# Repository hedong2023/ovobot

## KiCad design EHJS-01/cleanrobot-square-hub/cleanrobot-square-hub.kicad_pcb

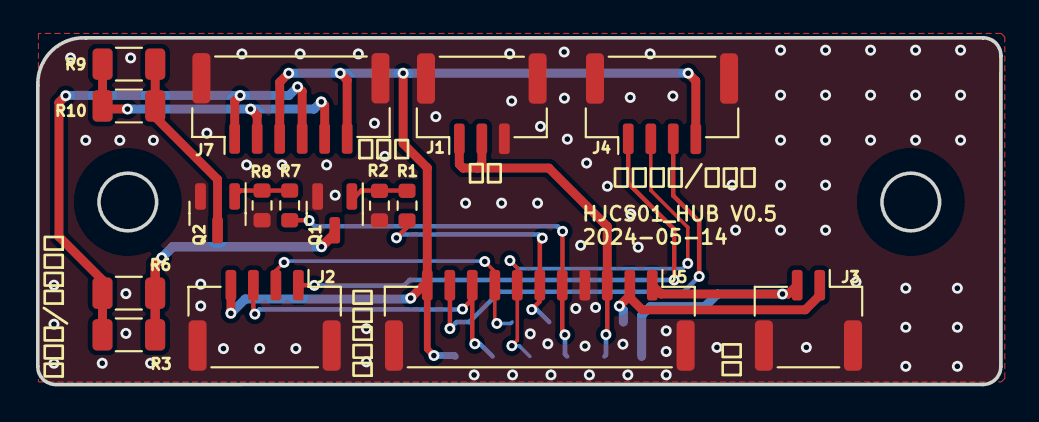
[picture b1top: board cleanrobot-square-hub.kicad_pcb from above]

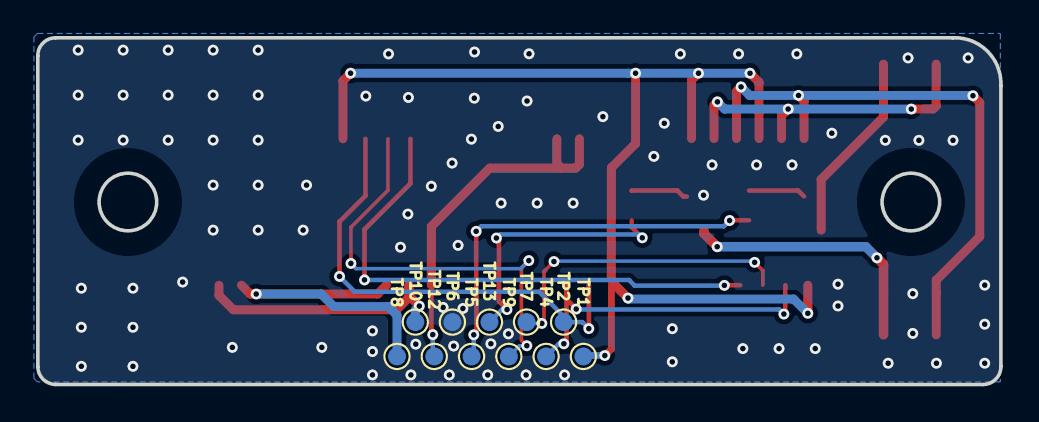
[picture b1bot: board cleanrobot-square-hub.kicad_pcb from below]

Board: 2 copper layers, 53.5 x 19.3 mm, 27 parts (11 on the bottom side), 18 nets.

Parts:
J1: GH1.25MM/3ASMT; JST_GH_BM03B-GHS-TBT_1x03-1MP_P1.25mm_Vertical
J2, J4: GH1.25MM/4ASMT; JST_GH_BM04B-GHS-TBT_1x04-1MP_P1.25mm_Vertical
J3: GH1.25MM/2ASMT; JST_GH_BM02B-GHS-TBT_1x02-1MP_P1.25mm_Vertical
J5: GH1.25MM/11ASMT; JST_GH_BM11B-GHS-TBT_1x11-1MP_P1.25mm_Vertical
J7: GH1.25MM/6ASMT; JST_GH_BM06B-GHS-TBT_1x06-1MP_P1.25mm_Vertical
Q1, Q2: SS8050; SOT-23
R1, R7: 1K; R_0603_1608Metric
R2, R8: 10K/1%; R_0603_1608Metric
R3, R6, R9, R10: 120R/250mW; R_1206_3216Metric
TP1: 5V; TestPoint_Pad_D1.0mm
TP2: SPRAY_FRONT; TestPoint_Pad_D1.0mm
TP4: SPRAY_BACK; TestPoint_Pad_D1.0mm
TP5: RED; TestPoint_Pad_D1.0mm
TP6: GND; TestPoint_Pad_D1.0mm
TP7: WATER1_DET_P; TestPoint_Pad_D1.0mm
TP8: SPEAKER_P; TestPoint_Pad_D1.0mm
TP9: WATER1_DET_N; TestPoint_Pad_D1.0mm
TP10: SPEAKER_N; TestPoint_Pad_D1.0mm
TP12: START; TestPoint_Pad_D1.0mm
TP13: GREEN; TestPoint_Pad_D1.0mm

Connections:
+5V: J2.4, J4.4, J5.11, J7.3, J7.6, TP1.1
/BLUE: J7.1, J7.4, R3.1, R6.1
/LED_BLUE: J5.6, R1.1, TP13.1
/LED_RED: J5.5, R7.1, TP5.1
/RED: J7.2, J7.5, R9.1, R10.1
/SPEAKER_N: J3.1, J5.2, TP10.1
/SPEAKER_P: J3.2, J5.1, TP8.1
/SPRAY_BACK: J2.3, J5.9, TP4.1
/SPRAY_FRONT: J4.3, J5.10, TP2.1
/START: J1.1, J1.2, J5.3, TP12.1
/WATER_COM: J2.1, J4.1
/WATER_DET_N: J4.2, J5.7, TP9.1
/WATER_DET_P: J2.2, J5.8, TP7.1
GND: J1.3, J1.MP (MountPin), J2.MP (MountPin), J3.MP (MountPin), J4.MP (MountPin), J5.4, J5.MP (MountPin), J7.MP (MountPin), Q1.2 (E), Q2.2 (E), R2.2, R8.2, TP6.1
unnamed: Q1.1 (B), R1.2, R2.1
unnamed: Q1.3 (C), R3.2, R6.2
unnamed: Q2.1 (B), R7.2, R8.1
unnamed: Q2.3 (C), R9.2, R10.2

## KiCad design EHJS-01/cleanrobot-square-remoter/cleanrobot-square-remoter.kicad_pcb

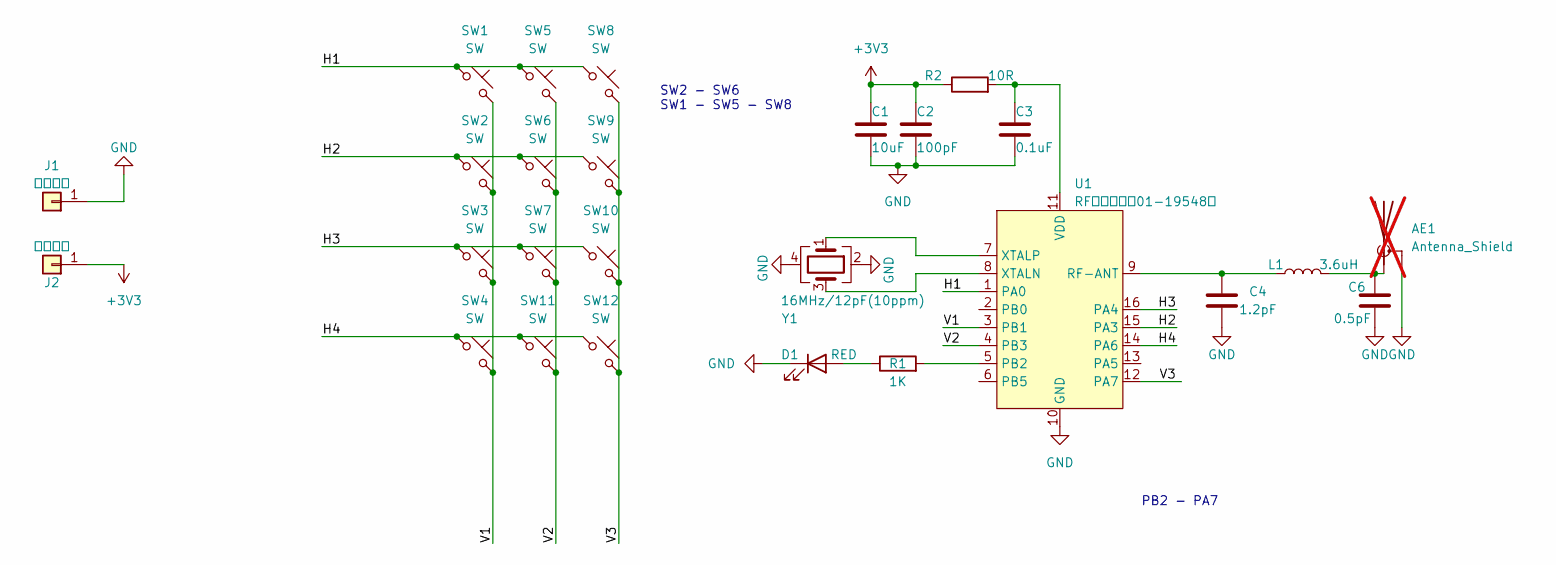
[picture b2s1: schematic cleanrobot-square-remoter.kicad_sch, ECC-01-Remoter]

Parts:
AE1: Antenna_Shield; Texas_SWRA117D_2.4GHz_Right; not fitted
C1: 10uF; C_0603_1608Metric
C2: 100pF; C_0603_1608Metric
C3: 0.1uF; C_0603_1608Metric
C4: 1.2pF; C_0603_1608Metric
C6: 0.5pF; C_0603_1608Metric
D1: RED; LED_1206_3216Metric
J1: 负极弹簧; Pad_THTPad_4.3x2.1mm_Drill3.1x0.9mm
J2: 正极弹簧; Pad_THTPad_4.3x2.1mm_Drill3.1x0.9mm
L1: 3.6uH; L_0603_1608Metric
R1: 1K; R_0603_1608Metric
R2: 10R; R_0603_1608Metric
SW1, SW2, SW3, SW4, SW5, SW6, SW7, SW8, SW9, SW10, SW11, SW12: SW; Dome_SLICE_ARC_6x6mm
U1: RF射频芯片（01-19548）; SOP-16_3.9x9.9mm_P1.27mm
Y1: 16MHz/12pF(10ppm); Oscillator_SMD_Abracon_ASE-4Pin_3.2x2.5mm

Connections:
+3V3: C1.1, C2.1, J2.1, R2.1
/H1: SW1.1, SW5.1, SW8.1, U1.1 (PA0)
/H2: SW2.1, SW6.1, SW9.1, U1.15 (PA3)
/H3: SW3.1, SW7.1, SW10.1, U1.16 (PA4)
/H4: SW4.1, SW11.1, SW12.1, U1.14 (PA6)
/V1: SW1.2, SW2.2, SW3.2, SW4.2, U1.3 (PB1)
/V2: SW5.2, SW6.2, SW7.2, SW11.2, U1.4 (PB3)
/V3: SW8.2, SW9.2, SW10.2, SW12.2, U1.12 (PA7)
GND: AE1.2 (Shield), C1.2, C2.2, C3.2, C4.1, C6.1, D1.1 (K), J1.1, U1.10 (GND), Y1.2, Y1.4
unnamed: AE1.1 (A), C6.2, L1.1
unnamed: D1.2 (A), R1.1
unnamed: R1.2, U1.5 (PB2)
unnamed: C4.2, L1.2, U1.9 (RF-ANT)
unnamed: C3.1, R2.2, U1.11 (VDD)
unnamed: U1.8 (XTALN), Y1.3
unnamed: U1.7 (XTALP), Y1.1

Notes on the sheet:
SW2 - SW6 SW1 - SW5 - SW8
PB2 - PA7

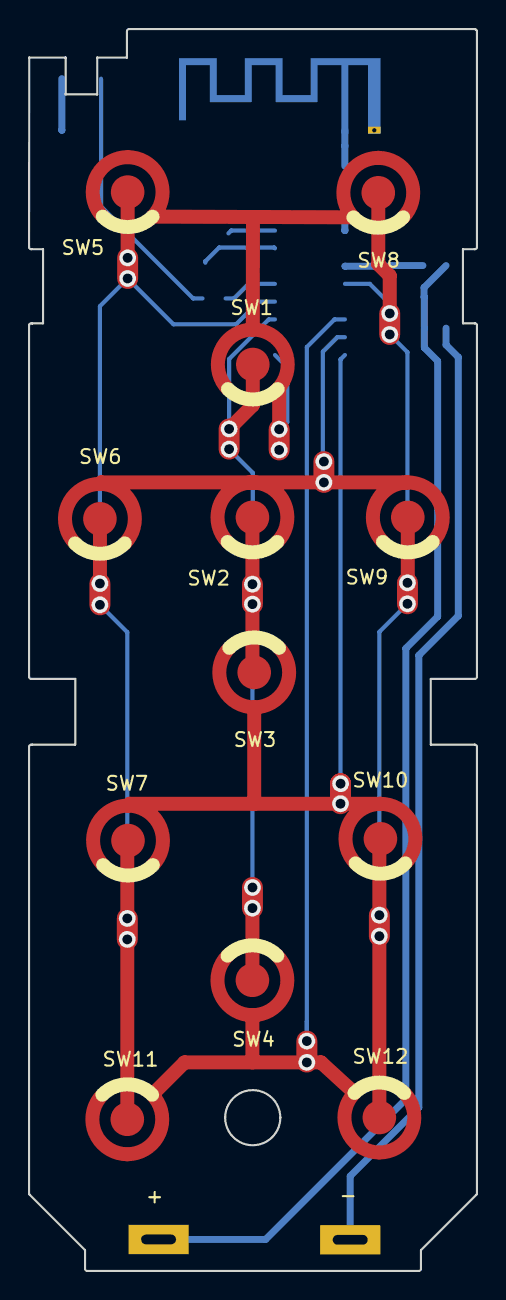
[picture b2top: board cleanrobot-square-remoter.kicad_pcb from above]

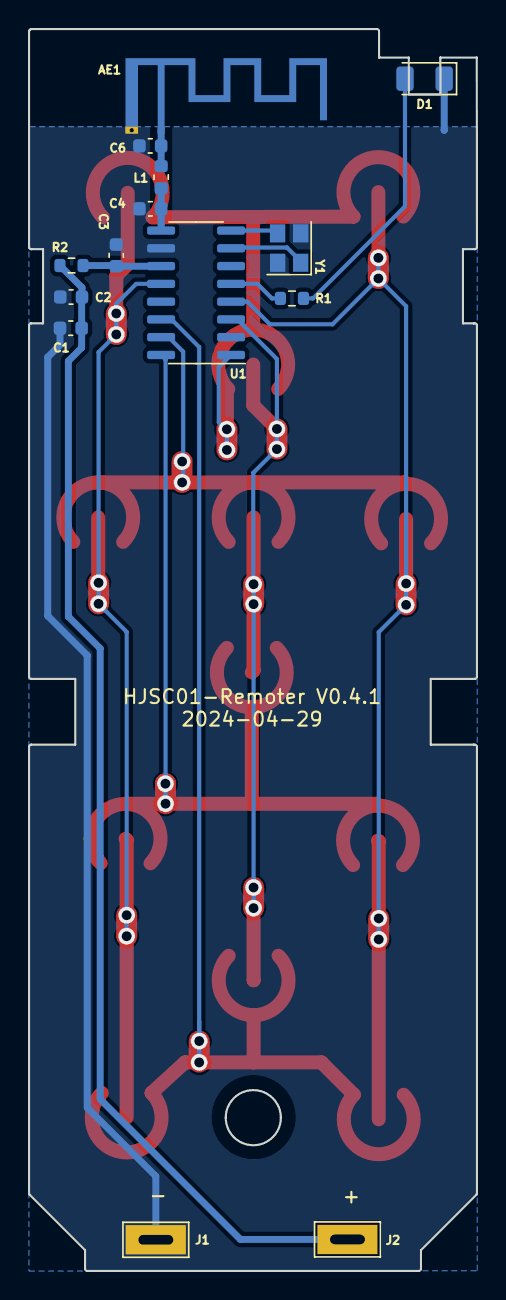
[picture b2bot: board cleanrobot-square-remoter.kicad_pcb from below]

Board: 2 copper layers, 32.0 x 88.7 mm, 26 parts (14 on the bottom side), 16 nets.

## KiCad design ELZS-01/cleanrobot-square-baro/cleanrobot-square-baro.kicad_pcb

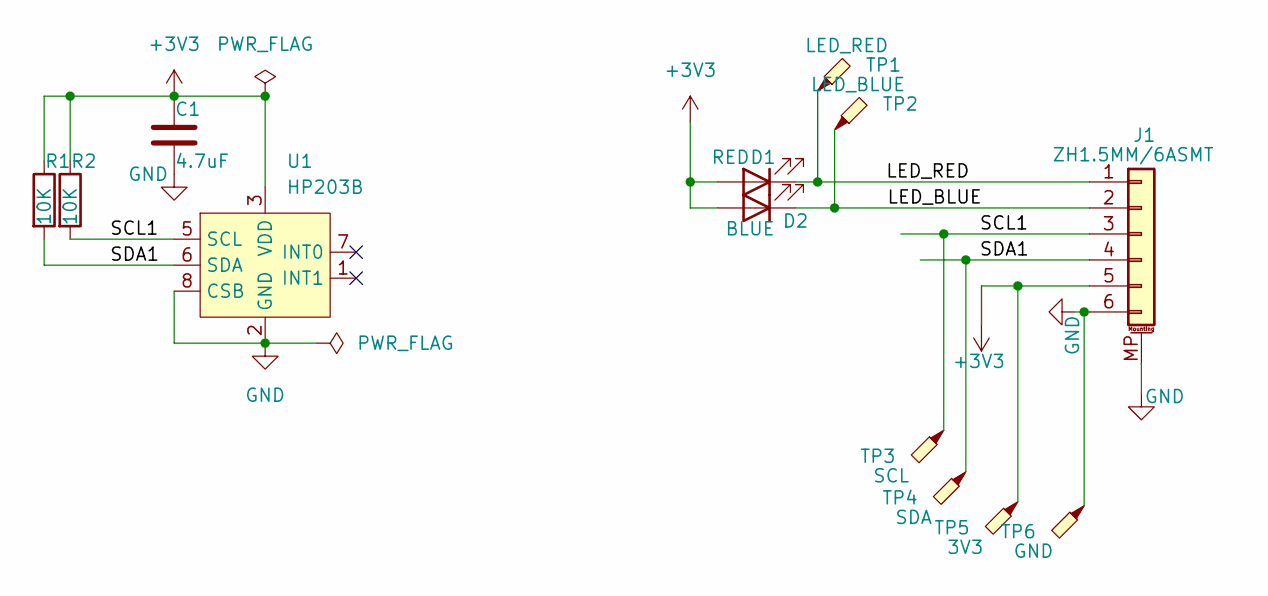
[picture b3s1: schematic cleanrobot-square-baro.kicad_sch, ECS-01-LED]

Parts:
C1: 4.7uF; C_0603_1608Metric
D1: RED; D_0603_1608Metric
D2: BLUE; D_0603_1608Metric
J1: ZH1.5MM/6ASMT; JST_ZH_B6B-ZR-SM4-TF_1x06-1MP_P1.50mm_Vertical
R1, R2: 10K; R_0603_1608Metric
TP1: LED_RED; TestPoint_Pad_D1.5mm
TP2: LED_BLUE; TestPoint_Pad_D1.5mm
TP3: SCL; TestPoint_Pad_D1.5mm
TP4: SDA; TestPoint_Pad_D1.5mm
TP5: 3V3; TestPoint_Pad_D1.5mm
TP6: GND; TestPoint_Pad_D1.5mm
U1: HP203B; HOPERF_LGA-8_3.8x3.6mm_P0.9mm

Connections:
+3V3: C1.1, D1.2 (A), D2.2 (A), J1.5, R1.1, R2.1, TP5.1, U1.3 (VDD)
/LED_BLUE: D2.1 (K), J1.2, TP2.1
/LED_RED: D1.1 (K), J1.1, TP1.1
/SCL1: J1.3, R2.2, TP3.1, U1.5 (SCL)
/SDA1: J1.4, R1.2, TP4.1, U1.6 (SDA)
GND: C1.2, J1.6, J1.MP (MountPin), TP6.1, U1.2 (GND), U1.8 (CSB)

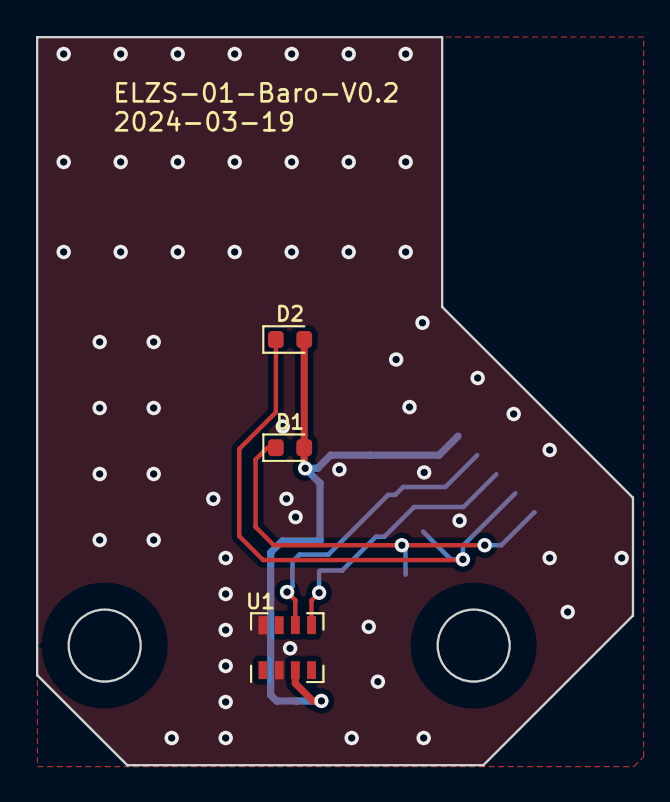
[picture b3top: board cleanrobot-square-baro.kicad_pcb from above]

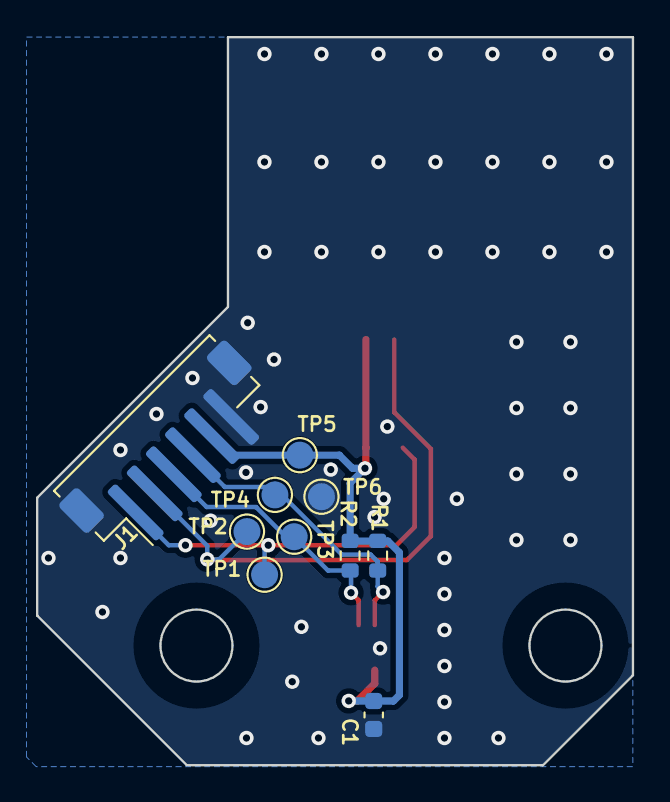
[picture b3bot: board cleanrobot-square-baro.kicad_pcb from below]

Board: 2 copper layers, 33.1 x 40.4 mm, 13 parts (10 on the bottom side), 6 nets.

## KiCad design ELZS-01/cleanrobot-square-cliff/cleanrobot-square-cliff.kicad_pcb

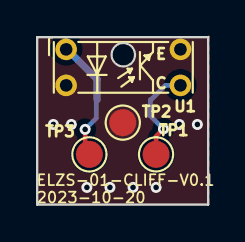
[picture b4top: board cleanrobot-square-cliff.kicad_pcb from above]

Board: 2 copper layers, 9.5 x 9.3 mm, 5 parts (1 on the bottom side), 3 nets.

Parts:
J1: SH1.25MM/3AWSMT; Molex_PicoBlade_53261-0371_1x03-1MP_P1.25mm_Horizontal
TP1: EDGE_DET_LT; TestPoint_Pad_D1.5mm
TP2: GND; TestPoint_Pad_D1.5mm
TP3: 3V3; TestPoint_Pad_D1.5mm
U1: ITR1203DT50A/TB; EverLight_ITR1203_7.5x2.6mm_P2.0mm

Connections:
/EDGE_DET_LT: J1.1, TP1.1, U1.3 (C)
GND: J1.2, J1.MP (MountPin), TP2.1, U1.2 (K), U1.4 (E)
unnamed: J1.3, TP3.1, U1.1 (A)

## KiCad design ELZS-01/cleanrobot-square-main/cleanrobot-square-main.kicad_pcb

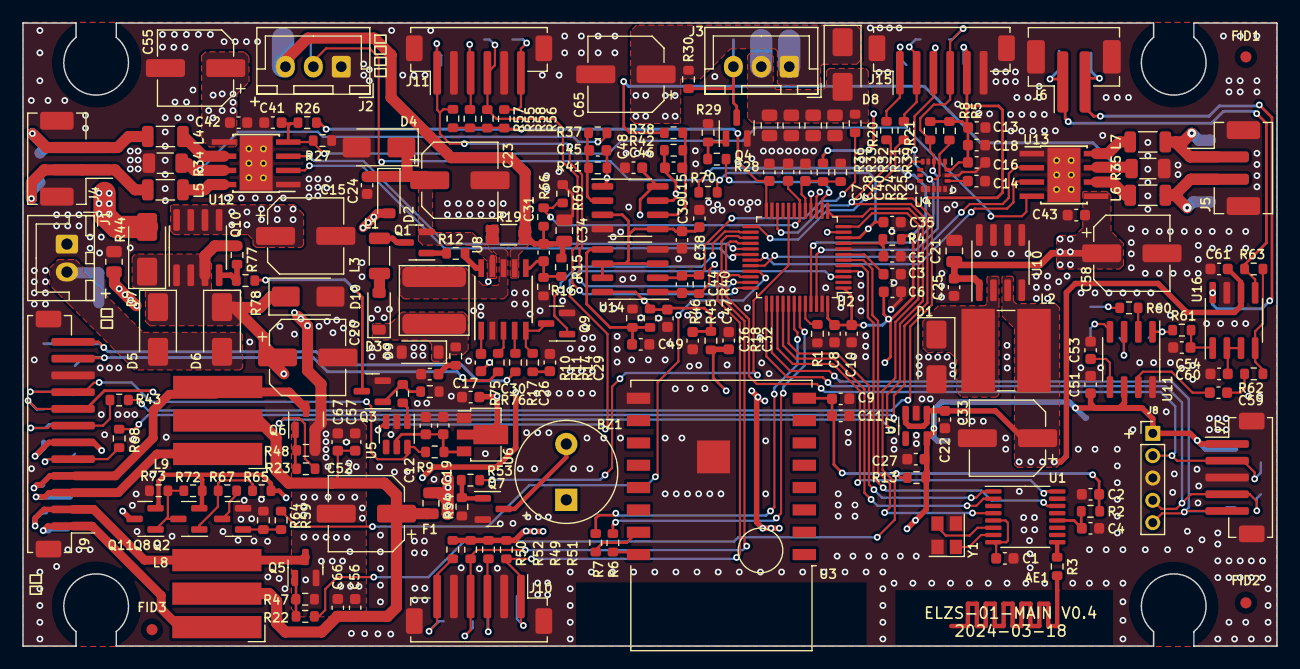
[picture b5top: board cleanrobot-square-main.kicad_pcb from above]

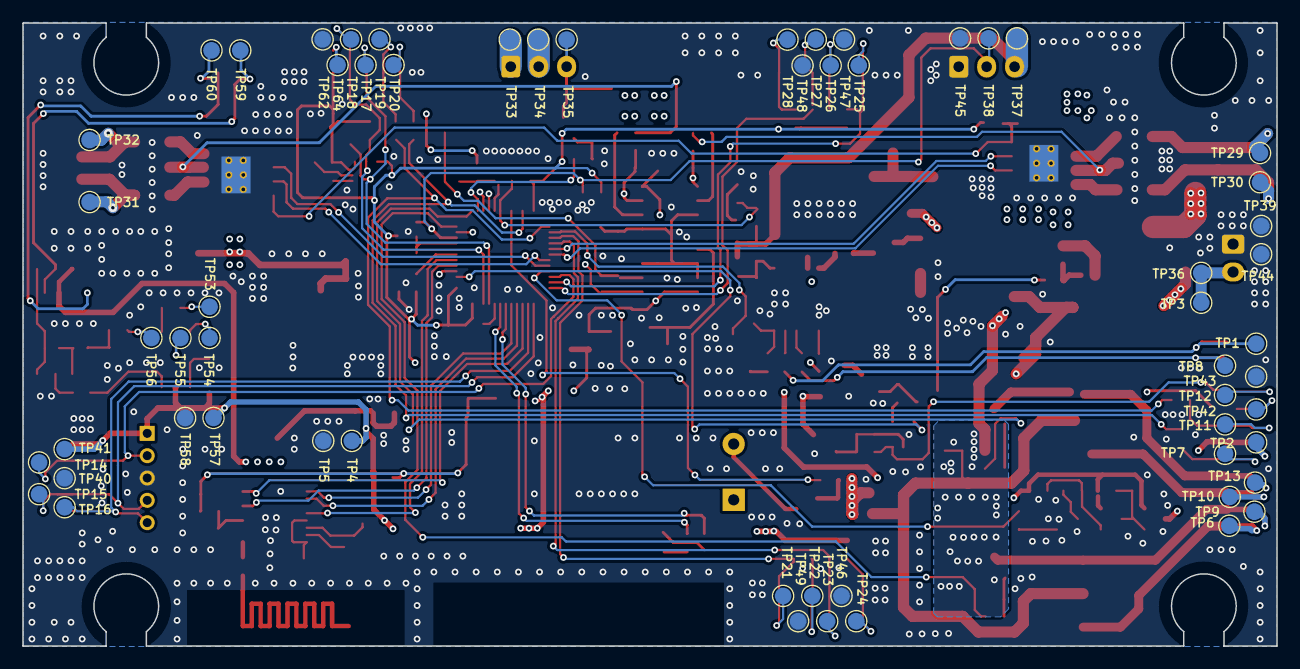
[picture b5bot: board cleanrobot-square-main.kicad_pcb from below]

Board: 4 copper layers, 112.3 x 55.8 mm, 261 parts (59 on the bottom side), 134 nets.

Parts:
AE1: NC/Antenna; Ovo_PA2401_2.4GHz_Right
BZ1: 85dB/5V; Buzzer_9x5.5RM5
C1, C2, C9, C22, C25, C27, C32, C36, C54, C56, C57, C60, C61: 1uF; C_0603_1608Metric
C3, C4, C5, C6, C7, C8, C11, C12, C16, C17, C24, C26, C28, C35, C38, C40, C41, C42, C43, C44, C45, C46, C47, C48, C49, C66, C67: 0.1uF; C_0603_1608Metric
C10: 4.7uF; C_0603_1608Metric
C13, C39: 10nF; C_0603_1608Metric
C14, C59: 0.47uF; C_0603_1608Metric
C15, C20, C55, C58, C65: 100uF/35V; CP_Elec_6.3x7.7
C18: 2.2uF; C_0603_1608Metric
C19, C51: 10uF; C_0603_1608Metric
C21, C34: 10uF/35V; C_0805_2012Metric
C23: 100uF/50V; CP_Elec_6.3x7.7
C29: 220nF; C_0603_1608Metric
C30, C53: 1nF; C_0603_1608Metric
C31: 1.5pF; C_0603_1608Metric
C33, C52: 470uF/10V; CP_Elec_6.3x7.7
D1, D5, D6, D7: SS34; D_SMA
D2, D3, D9: SS14; D_SOD-123
D4, D10: SMAJ24CA; D_SMA
D8: 1N4004; D_SMA
F1: MF-PSMF050X; Fuse_0805_2012Metric
FID1, FID2, FID3: NC/Fiducial; Fiducial_1mm_Mask2mm
J1: XHB2.54MM/2A; JST_XH_B2B-XH-A_1x02_P2.50mm_Vertical
J2, J3: XH2.54MM/3A; JST_XH_B3B-XH-A_1x03_P2.50mm_Vertical
J4, J5, J6: PH2.0MM/2ASMT; JST_PH_B2B-PH-SM4-TB_1x02-1MP_P2.00mm_Vertical
J7: ZH1.5MM/5ASMT; JST_ZH_B5B-ZR-SM4-TF_1x05-1MP_P1.50mm_Vertical
J8: 2.0MM/5ASMT; PinHeader_1x05_P2.00mm_Vertical
J9: ZH1.5MM/12ASMT; JST_ZH_B12B-ZR-SM4-TF_1x12-1MP_P1.50mm_Vertical
J10, J11, J15: ZH1.5MM/6ASMT; JST_ZH_B6B-ZR-SM4-TF_1x06-1MP_P1.50mm_Vertical
L1, L4, L5, L6, L7: 120R@100MHz/3A; L_1206_3216Metric
L2: 68uH; L_GZJ_CD75
L3: 100uH; L_GZJ_WNR6045
L8, L9: 10/500uH; L_WLJ_CD0805
Q1: HSS6107; SOT-23
Q2, Q3, Q4, Q7: SS8050; SOT-23
Q5, Q6: CJ2310; SOT-23
Q8: SS8550; SOT-23
Q9: SI2302; SOT-23
Q10: NCE40P13S; SOIC-8_3.9x4.9mm_P1.27mm
Q11: SI2309; SOT-23
R1, R9, R10, R11, R29, R45, R47, R48, R51, R52, R54, R57, R58, R61, R62, R63, R64, R70, R76, R77, R78: 10K/1%; R_0603_1608Metric
R2, R3, R4, R6, R7, R13, R18, R60: 0R; R_0603_1608Metric
R5, R8: 4.7K/1%; R_0603_1608Metric
R12: 51R; R_0603_1608Metric
R14, R49, R50, R55, R56: 120R; R_0603_1608Metric
R15: 1.5M/1%; R_0603_1608Metric
R16: 120K/1%; R_0603_1608Metric
R17: 100R; R_0603_1608Metric
R19: 0.5R/1%; R_1206_3216Metric
R20, R21, R43, R68: 330R; R_0603_1608Metric
R22, R23, R28, R53, R59, R75: 1K; R_0603_1608Metric
R24, R66: 1M/1%; R_0603_1608Metric
R25, R69: 100K/1%; R_0603_1608Metric
R26: 6.8K/1%; R_0603_1608Metric
R27: 3.3K/1%; R_0603_1608Metric
R30: NC/10K/1%; R_0603_1608Metric
R31, R32, R33, R36: 0.1R; R_0805_2012Metric
R34, R35: 0.033R/1%(1W); R_1206_3216Metric
R37, R38, R39: 15K/1%; R_0603_1608Metric
R40, R41, R42: 51K/1%; R_0603_1608Metric
R44: 0R; R_0805_2012Metric
R46: 2K/1%; R_0603_1608Metric
R65, R73: 10K; R_0603_1608Metric
R67: 100K; R_0603_1608Metric
R72: 2K; R_0603_1608Metric
TP1: CHG_DONE_LED; TestPoint_Pad_D1.5mm
TP2: V_CHRG_O; TestPoint_Pad_D1.5mm
TP3, TP36: 24V; TestPoint_Pad_D1.5mm
TP4, TP57: 3V3; TestPoint_Pad_D1.5mm
TP5, TP39, TP40, TP43, TP44, TP45, TP46, TP47, TP48, TP49, TP58, TP62: GND; TestPoint_Pad_D1.5mm
TP6: SPRAY_FRONT_P; TestPoint_Pad_D1.5mm
TP7: LED_RED; TestPoint_Pad_D1.5mm
TP8: CHG_ON_LED; TestPoint_Pad_D1.5mm
TP9: SPRAY_FRONT_N; TestPoint_Pad_D1.5mm
TP10: SPRAY_BACK_P; TestPoint_Pad_D1.5mm
TP11: LED_BLUE; TestPoint_Pad_D1.5mm
TP12: START; TestPoint_Pad_D1.5mm
TP13: SPRAY_BACK_N; TestPoint_Pad_D1.5mm
TP14: SWDIO; TestPoint_Pad_D1.5mm
TP15: SWCLK; TestPoint_Pad_D1.5mm
TP16: UART2_RX; TestPoint_Pad_D1.5mm
TP17: SCL1; TestPoint_Pad_D1.5mm
TP18: SDA1; TestPoint_Pad_D1.5mm
TP19: BLUE; TestPoint_Pad_D1.5mm
TP20: RED; TestPoint_Pad_D1.5mm
TP21: EDGE_DET_LT; TestPoint_Pad_D1.5mm
TP22: EDGE_DET_LT_LED; TestPoint_Pad_D1.5mm
TP23: EDGE_DET_RT; TestPoint_Pad_D1.5mm
TP24: EDGE_DET_RT_LED; TestPoint_Pad_D1.5mm
TP25: EDGE_DET_LB; TestPoint_Pad_D1.5mm
TP26: EDGE_DET_LB_LED; TestPoint_Pad_D1.5mm
TP27: EDGE_DET_RB; TestPoint_Pad_D1.5mm
TP28: EDGE_DET_RB_LED; TestPoint_Pad_D1.5mm
TP29: MOTOR_LF_OUT1; TestPoint_Pad_D1.5mm
TP30: MOTOR_LF_OUT2; TestPoint_Pad_D1.5mm
TP31: MOTOR_RT_OUT1; TestPoint_Pad_D1.5mm
TP32: MOTOR_RT_OUT2; TestPoint_Pad_D1.5mm
TP33: VDD; TestPoint_Pad_D1.5mm
TP34: FAN_OUT_N; TestPoint_Pad_D1.5mm
TP35: FAN_OUT_PWM; TestPoint_Pad_D1.5mm
TP37: BATT; TestPoint_Pad_D1.5mm
TP38: TEMP; TestPoint_Pad_D1.5mm
TP41, TP42, TP64: +3V3; TestPoint_Pad_D1.5mm
TP53: DO; TestPoint_Pad_D1.5mm
TP54: CLK; TestPoint_Pad_D1.5mm
TP55: DI; TestPoint_Pad_D1.5mm
TP56: CS; TestPoint_Pad_D1.5mm
TP59: SPEAKER_P; TestPoint_Pad_D1.5mm
TP60: SPEAKER_N; TestPoint_Pad_D1.5mm
U1: LT8920; TSSOP-16_4.4x5mm_P0.65mm
U2: MM32F0144C6P; LQFP-48_7x7mm_P0.5mm
U3: BT3L; Tuya_BT3L
U4: MPU-6887; LGA-16_3x3mm_P0.5mm_LayoutBorder3x5y
U5: PMS150C-U06(0x2B191B); SOT-23-6
U6: HT7533-1-SOT89; SOT-89-3
U7: RT9013-33; SOT-23-5
U8: CN3765; SSOP-10_3.9x4.9mm_P1.00mm
U10: XL1509-5.0E1; SOIC-8_3.9x4.9mm_P1.27mm
U11: WT588F02B-8S-B2(通用); SOIC-8_3.9x4.9mm_P1.27mm
U12, U13: DRV8870DDA; Texas_HTSOP-8-1EP_3.9x4.9mm_P1.27mm_EP2.95x4.9mm_Mask2.4x3.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
U14, U15: LMV358TP-SR; SOIC-8_3.9x4.9mm_P1.27mm
U16: 8002A; SOIC-8_3.9x4.9mm_P1.27mm
Y1: 12MHz/22pF(10ppm); Oscillator_SMD_Abracon_ASE-4Pin_3.2x2.5mm

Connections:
+3.3VA: C36.1, C47.1, C48.1, R18.2, R45.1, U14.8 (V+), U15.8 (V+)
+3.3VP: C2.1, C9.1, C11.1, R2.1, R13.2, U3.8 (VDD_BAT)
+3V3: C6.2, C7.2, C8.2, C10.2, C13.2, C16.2, C18.2, C27.1, C32.1, C51.1, J7.1, J8.1, J9.8, J15.5, R4.2, R5.2, R8.2, R13.1, R18.1, R26.1, R49.1, R50.1, R51.1, R52.1, R55.1, R56.1, R57.1, R58.1, R70.1, TP4.1, TP41.1, TP42.1, TP57.1, TP64.1, U2.1 (VDD), U2.24 (VDD), U2.48 (VDD), U4.1 (VDDIO), U4.5 (CS), U4.16 (VDD), U7.5 (VOUT), U11.6 (VDD)
+5V: BZ1.1 (-), C22.1, C33.1, C61.1, F1.1, L2.2, U7.1 (VIN), U7.3 (EN), U10.3 (FB), U16.6 (VDD)
+24V: D2.2 (A), D5.2 (A), D6.2 (A), J1.2, TP3.1, TP36.1
+BATT: C31.1, C34.1, D7.2 (A), J2.3, R15.1, R19.2, R66.1, TP37.1, U8.7 (BAT)
/driver/VREF55: C38.1, C39.1, U14.3 (+), U14.6 (-), U14.7, U15.3 (+), U15.5 (+)
/main/BLE_MCU_RXD: R6.2, U2.43 (PB7)
/main/BLE_MCU_TXD: R7.2, U2.42 (PB6)
/main/MISO: U1.2 (MISO), U2.40 (PB4)
/main/MOSI: U1.1 (MOSI), U2.41 (PB5)
/main/RF_REST: U1.4 (~RST), U2.6 (PF1)
/main/SCK: U1.16 (SCK), U2.39 (PB3)
/main/SCS: U1.14 (SS), U2.5 (PF0)
/peripheral/VOICE_BUSY: R61.1, TP56.1, U11.1 (PC2/CS)
/peripheral/V_CHRG_O: J9.6, Q11.3 (D), TP2.1
/power/3V3_OFF: C12.1, C19.1, R9.1, U5.5 (VDD), U6.3 (VOUT)
/power/VIN: C17.1, C20.1, D5.1 (K), D6.1 (K), D7.1 (K), D10.1 (K), Q10.1 (S), Q10.2 (S), Q10.3 (S), R77.2, U6.2 (VIN)
ADC_BATT: C28.1, R66.2, R69.1, U2.18 (PB0)
ADC_FAN_MOTOR: C44.2, R40.2, U2.11 (PA1), U14.1
ADC_LEFT_MOTOR: C45.2, R41.2, U2.15 (PA5), U15.1
ADC_RIGHT_MOTOR: C46.2, R42.2, U2.16 (PA6), U15.7
ADC_SYS: C40.1, R24.2, R25.1, U2.17 (PA7)
BELL: R53.1, U2.20 (PB2)
CHG_DONE_LED: J9.12, R11.1, TP1.1
CHG_LED_SW: R59.1, U2.33 (PA12)
CHG_ON_LED: J9.11, R10.1, TP8.1
EDGE_DET_LB: J11.1, R57.2, TP25.1, U2.35 (PF6)
EDGE_DET_LT: J10.1, R51.2, TP21.1, U2.27 (PB14)
EDGE_DET_RB: J11.4, R58.2, TP27.1, U2.36 (PF7)
EDGE_DET_RT: J10.4, R52.2, TP23.1, U2.28 (PB15)
EN_CHRG: Q9.1 (G), U2.26 (PB13)
GND: C1.2, C2.2, C3.1, C4.2, C5.1, C6.1, C7.1, C8.1, C9.2, C10.1, C11.2, C12.2, C13.1, C14.1, C15.2, C16.1, C17.2, C18.1, C19.2, C20.2, C21.2, C22.2, C23.2, C24.2, C25.2, C27.2, C28.2, C29.2, C30.2, C32.2, C33.2, C34.2, C35.2, C36.2, C38.2, C39.2, C40.2, C41.2, C42.2, C43.2, C47.2, C48.2, C49.2, C51.2, C53.2, C54.2, C55.2, C58.2, C60.1, C61.2, C65.2, D1.2 (A), D4.2 (A), D9.2 (A), D10.2 (A), J1.1, J2.1, J4.MP (MountPin), J5.MP (MountPin), J6.MP (MountPin), J7.3, J7.MP (MountPin), J8.3, J9.10, J9.MP (MountPin), J10.2, J10.5, J10.MP (MountPin), J11.2, J11.5, J11.MP (MountPin), J15.6, J15.MP (MountPin), Q2.2 (E), Q3.2 (E), Q4.2 (E), Q7.2 (E), Q9.2 (S), R1.1, R16.2, R25.2, R27.2, R29.1, R31.2, R32.2, R33.2, R34.2, R35.2, R36.2, R44.2, R46.2, R54.2, R64.2, R69.2, R73.1, R76.1, TP5.1, TP39.1, TP40.1, TP43.1, TP44.1, TP45.1, TP46.1, TP47.1, TP48.1, TP49.1, TP58.1, TP62.1, U1.15 (VSS), U2.8 (VSSA), U2.23 (VSS), U2.47 (VSS), U3.9 (GND), U3.17 (PAD), U4.4 (AD0/SDO), U4.9 (RESV), U4.10 (RESV), U4.11 (RESV), U4.12 (RESV), U4.13 (GND), U4.15 (RECV), U5.2 (GND), U6.1 (GND), U7.2 (GND), U8.2 (GND), U10.4 (EN), U10.5 (GND), U10.6 (GND), U10.7 (GND), U10.8 (GND), U11.8 (GND), U12.1 (GND), U12.9 (GND), U13.1 (GND), U13.9 (GND), U14.4 (V-), U15.4 (V-), U16.7 (GND), Y1.2, Y1.4
GNDA: C52.2, C56.2, C57.2, C66.2, C67.2, Q5.2 (S), Q6.2 (S), R44.1, R47.2, R48.2
LED_BLUE: R21.1, R43.1, U2.25 (PB12)
LED_RED: R20.1, R68.1, U2.22 (PB11)
unnamed: AE1.1 (A), R3.2
unnamed: BZ1.2 (+), Q7.3 (C)
unnamed: C29.1, R14.2
unnamed: C30.1, R17.2
unnamed: C52.1, C56.1, C57.1, C66.1, C67.1, F1.2, L8.1, L9.1
unnamed: C59.2, R62.1
unnamed: D1.1 (K), L2.1, U10.2 (OUT)
unnamed: D3.2 (A), L1.2
unnamed: D3.1 (K), D9.1 (K), L3.1, R17.1
unnamed: D8.2 (A), J3.2, R31.1, R32.1, R33.1, R36.1, R39.1, TP34.1
unnamed: J3.3, Q4.3 (C), R30.2, TP35.1
unnamed: J4.1, L5.2, TP30.1
unnamed: J4.2, L4.2, TP29.1
unnamed: J5.1, L7.2, TP32.1
unnamed: J5.2, L6.2, TP31.1
unnamed: J6.1, R63.2, TP59.1, U16.5 (VO1)
unnamed: J6.2, TP60.1, U16.8 (VO2)
unnamed: J9.5, R68.2, TP7.1
unnamed: J9.7, R43.2, TP11.1
unnamed: J10.3, R49.2, TP22.1
unnamed: J10.6, R50.2, TP24.1
unnamed: J11.3, R55.2, TP26.1
unnamed: J11.6, R56.2, TP28.1
unnamed: J15.1, R20.2, TP20.1
unnamed: J15.2, R21.2, TP19.1
unnamed: L1.1, Q1.3 (D)
unnamed: Q1.1 (G), R12.1
unnamed: Q2.1 (B), R59.2, R64.1
unnamed: Q2.3 (C), R67.1
unnamed: Q3.1 (B), R75.1, R76.2
unnamed: Q3.3 (C), R78.1
unnamed: Q4.1 (B), R28.2, R29.2
unnamed: Q5.1 (G), R22.2, R47.1
unnamed: Q6.1 (G), R23.2, R48.1
unnamed: Q7.1 (B), R53.2, R54.1
unnamed: Q8.1 (B), R65.1, R67.2
unnamed: Q9.3 (D), R14.1, U8.5 (COM)
unnamed: Q10.4 (G), R77.1, R78.2
unnamed: Q8.3 (C), Q11.1 (G), R72.1, R73.2
unnamed: R3.1, U1.9 (ANTB)
unnamed: C4.1, R2.2, U1.12 (LDO_IN)
unnamed: C1.1, U1.5 (LDO_OUT), U1.8 (PLL_VDD)
unnamed: U1.7 (XTALI), Y1.1
unnamed: U1.6 (XTALO), Y1.3
unnamed: R1.2, U2.44 (BOOT0)
unnamed: C3.2, U2.7 (NRST)
unnamed: C5.2, R4.1, U2.9 (VDDA)
unnamed: R6.1, U3.16 (TL_B1)
unnamed: R7.1, U3.15 (TL_B7)
unnamed: C14.2, U4.14 (REGOUT)
unnamed: R75.2, U5.1 (PA4)
unnamed: L3.2, R19.1, U8.8 (CSP)
unnamed: R12.2, U8.10 (DRV)
unnamed: C31.2, R15.2, R16.1, U8.6 (FB)
unnamed: C26.2, U8.1 (VG)
unnamed: R10.2, U8.3 (~CHRG)
unnamed: R11.2, U8.4 (~DONE)
unnamed: R60.2, U11.2 (PC1/SO)
unnamed: TP55.1, U11.3 (PI0/SI)
unnamed: TP54.1, U11.4 (PI1/SCK)
unnamed: C53.1, U11.5 (PWMN)
unnamed: C59.1, U11.7 (PWMP/DAC)
unnamed: R34.1, R37.1, U12.7 (ISEN)
unnamed: L4.1, U12.6 (OUT1)
unnamed: L5.1, U12.8 (OUT2)
unnamed: C41.1, R26.2, R27.1, U12.4 (VREF), U13.4 (VREF)
unnamed: R35.1, R38.1, U13.7 (ISEN)
unnamed: L6.1, U13.6 (OUT1)
unnamed: L7.1, U13.8 (OUT2)
unnamed: C44.1, R39.2, R40.1, U14.2 (-)
unnamed: C49.1, R45.2, R46.1, U14.5 (+)
unnamed: C45.1, R37.2, R41.1, U15.2 (-)
unnamed: C46.1, R38.2, R42.1, U15.6 (-)
unnamed: C60.2, U16.2 (BYPASS), U16.3 (IN+)
unnamed: R62.2, R63.1, U16.4 (IN-)
unnamed: C54.1, R61.2, U16.1 (~SD)
PWM_FAN: R28.1, U2.14 (PA4)
PWM_LEFT1: U2.29 (PA8), U12.3 (IN1)
PWM_LEFT2: U2.30 (PA9), U12.2 (IN2)
PWM_RIGHT1: U2.31 (PA10), U13.3 (IN1)
PWM_RIGHT2: U2.32 (PA11), U13.2 (IN2)
SCL1: J15.3, R5.1, TP17.1, U2.45 (PB8), U4.2 (SCL/SCLK)
SDA1: J15.4, R8.1, TP18.1, U2.46 (PB9), U4.3 (SDA/SDI)
SPRAY_BACK: R23.1, U2.13 (PA3)
SPRAY_BACK_N: J9.4, L9.2, Q6.3 (D), TP13.1
SPRAY_BACK_P: J9.3, L9.3, TP10.1
SPRAY_FRONT: R22.1, U2.12 (PA2)
SPRAY_FRONT_N: J9.2, L8.2, Q5.3 (D), TP9.1
SPRAY_FRONT_P: J9.1, L8.3, TP6.1
START: J9.9, R9.2, TP12.1, U5.6 (PA3)
SWCLK: J7.4, J8.4, TP15.1, U2.37 (PA14)
SWDIO: J7.2, J8.2, TP14.1, U2.34 (PA13)
TEMP: C35.1, J2.2, R70.2, TP38.1, U2.10 (PA0)
TSD_DATA: U2.3 (PC14), U5.3 (PA6)
UART2_RX: J7.5, J8.5, TP16.1, U2.38 (PA15)
VDD: C15.1, C21.1, C25.1, C42.1, C43.1, C55.1, C58.1, C65.1, D8.1 (K), J3.1, Q10.5 (D), Q10.6 (D), Q10.7 (D), Q10.8 (D), R24.1, R30.1, TP33.1, U10.1 (VIN), U12.5 (VM), U13.5 (VM)
VOICE_DATA: R60.1, TP53.1, U2.4 (PC15)
V_CHRG_I: C23.1, C24.1, C26.1, D2.1 (K), D4.1 (K), Q1.2 (S), Q8.2 (E), Q11.2 (S), R65.2, R72.2, U8.9 (VCC)

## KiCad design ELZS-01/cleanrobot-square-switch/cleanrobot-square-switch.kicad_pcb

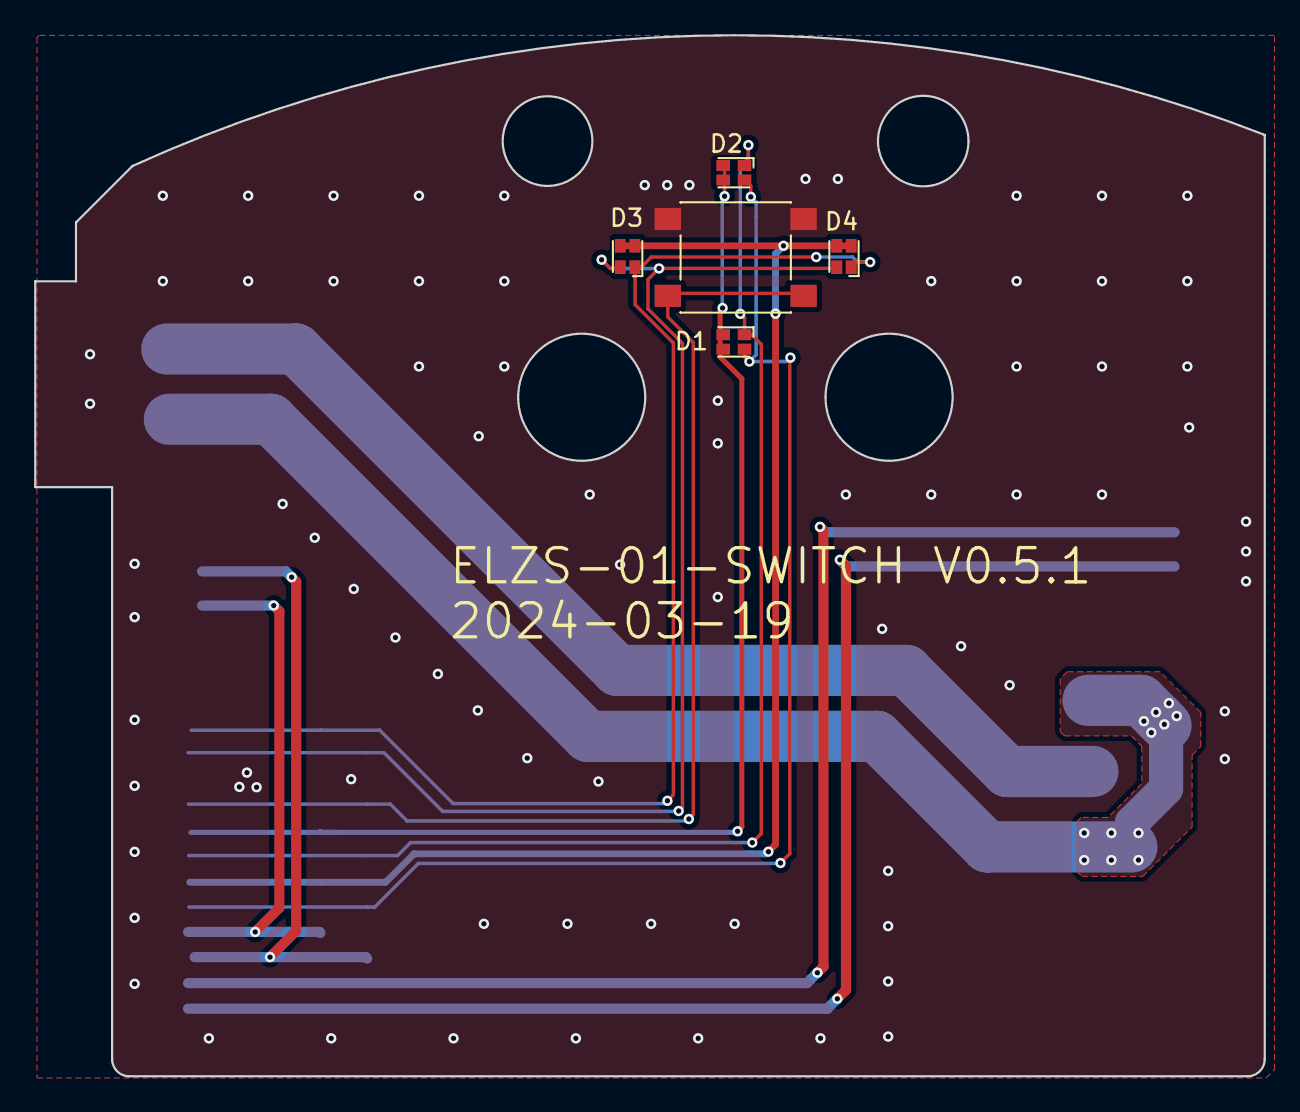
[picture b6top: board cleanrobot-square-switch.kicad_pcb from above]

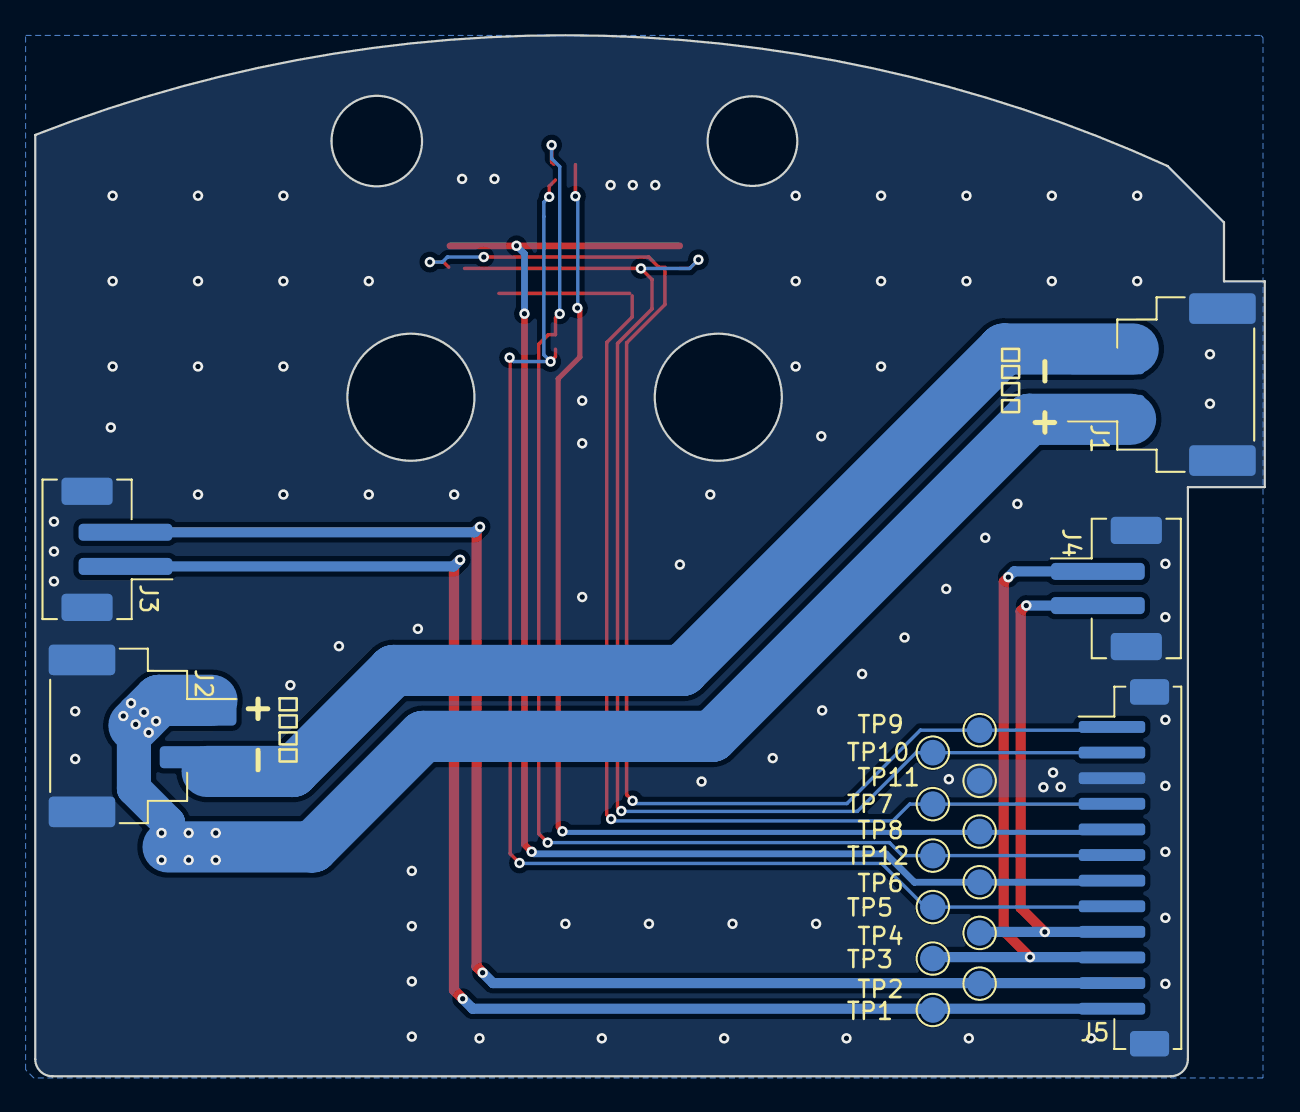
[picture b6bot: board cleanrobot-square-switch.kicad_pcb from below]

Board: 2 copper layers, 72.0 x 61.0 mm, 22 parts (17 on the bottom side), 14 nets.

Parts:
D1, D2: LED_Dual_Red_Blue_AKAK; LED_Dual_1.6x1.5mm
D3, D4: LED_Dual_Orange_Green_AKAK; LED_Dual_1.6x1.5mm
J1, J2: XHB2.54MM/2AWSMT; JST_XHB_S2B-XHB-SM4-TB_1x02-1MP_P2.50mm_Horizontal
J3, J4: PH2.0MM/2ASMT; JST_PH_B2B-PH-SM4-TB_1x02-1MP_P2.00mm_Vertical
J5: ZH1.5MM/12AWSMT; JST_ZH_B12B-ZR-SM4-TF_1x12-1MP_P1.50mm_Vertical
SW1: 6x6x5mm; SW_Push_1P1T_NO_6x6mm_H5.0mm
TP1: SPRAY_FRONT_P; TestPoint_Pad_D1.5mm
TP2: SPRAY_FRONT_N; TestPoint_Pad_D1.5mm
TP3: SPRAY_BACK_P; TestPoint_Pad_D1.5mm
TP4: SPRAY_BACK_N; TestPoint_Pad_D1.5mm
TP5: LED_RED; TestPoint_Pad_D1.5mm
TP6: VPP; TestPoint_Pad_D1.5mm
TP7: START; TestPoint_Pad_D1.5mm
TP8: 3V3; TestPoint_Pad_D1.5mm
TP9: CHG_DONE_LED; TestPoint_Pad_D1.5mm
TP10: CHG_ON_LED; TestPoint_Pad_D1.5mm
TP11: GND; TestPoint_Pad_D1.5mm
TP12: LED_BLUE; TestPoint_Pad_D1.5mm

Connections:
+3V3: D1.1 (A1), D1.3 (A2), D2.1 (A1), D2.3 (A2), J5.5, TP8.1
/CHG_DONE_LED: D3.4 (K2), D4.4 (K2), J5.1, TP9.1
/CHG_ON_LED: D3.2 (K1), D4.2 (K1), J5.2, TP10.1
/LED_BLUE: D1.4 (K2), D2.4 (K2), J5.6, TP12.1
/LED_RED: D1.2 (K1), D2.2 (K1), J5.8, TP5.1
/SPRAY_BACK_N: J4.2, J5.9, TP4.1
/SPRAY_BACK_P: J4.1, J5.10, TP3.1
/SPRAY_FRONT_N: J3.2, J5.11, TP2.1
/SPRAY_FRONT_P: J3.1, J5.12, TP1.1
/START: J5.4, SW1.2, TP7.1
GND: J1.MP (MountPin), J2.MP (MountPin), J3.MP (MountPin), J4.MP (MountPin), J5.3, J5.MP (MountPin), SW1.1, TP11.1
unnamed: J1.1, J2.1
unnamed: J1.2, J2.2
VPP: D3.1 (A1), D3.3 (A2), D4.1 (A1), D4.3 (A2), J5.7, TP6.1

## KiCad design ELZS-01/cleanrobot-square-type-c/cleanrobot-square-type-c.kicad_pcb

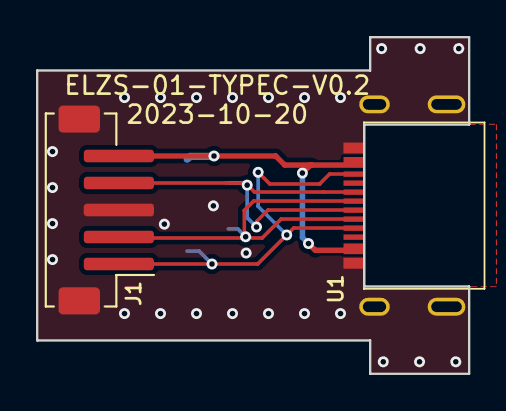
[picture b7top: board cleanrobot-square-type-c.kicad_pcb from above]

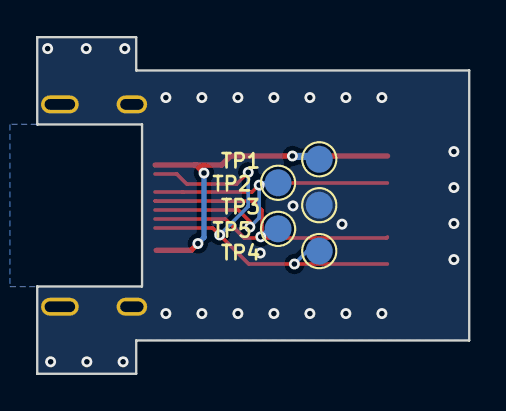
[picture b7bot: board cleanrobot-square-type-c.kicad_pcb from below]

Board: 2 copper layers, 24.0 x 18.7 mm, 7 parts (5 on the bottom side), 5 nets.

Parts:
J1: ZH1.5MM/5ASMT; JST_ZH_B5B-ZR-SM4-TF_1x05-1MP_P1.50mm_Vertical
TP1: 3V3; TestPoint_Pad_D1.5mm
TP2: SWDIO; TestPoint_Pad_D1.5mm
TP3: GND; TestPoint_Pad_D1.5mm
TP4: UART2_RX; TestPoint_Pad_D1.5mm
TP5: SWCLK; TestPoint_Pad_D1.5mm
U1: TYPE-C 16P CB1.6 073; USB_TYPE-C 16P CB1.6 073

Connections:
+3V3: J1.5, TP1.1, U1.A4 (VBUS), U1.A9 (VBUS), U1.B4 (VBUS), U1.B9 (VBUS)
/SWCLK: J1.2, TP5.1, U1.A7 (D-/DN1), U1.B7 (D-/DN2)
/SWDIO: J1.4, TP2.1, U1.A6 (D+/DP1), U1.B6 (D+/DP2)
/UART2_RX: J1.1, TP4.1, U1.A5 (CC1), U1.B5 (CC2)
GND: J1.3, J1.MP (MountPin), TP3.1, U1.25 (GND), U1.26 (GND), U1.27 (GND), U1.28 (GND), U1.A1 (GND), U1.A12 (GND), U1.B1 (GND), U1.B12 (GND)
